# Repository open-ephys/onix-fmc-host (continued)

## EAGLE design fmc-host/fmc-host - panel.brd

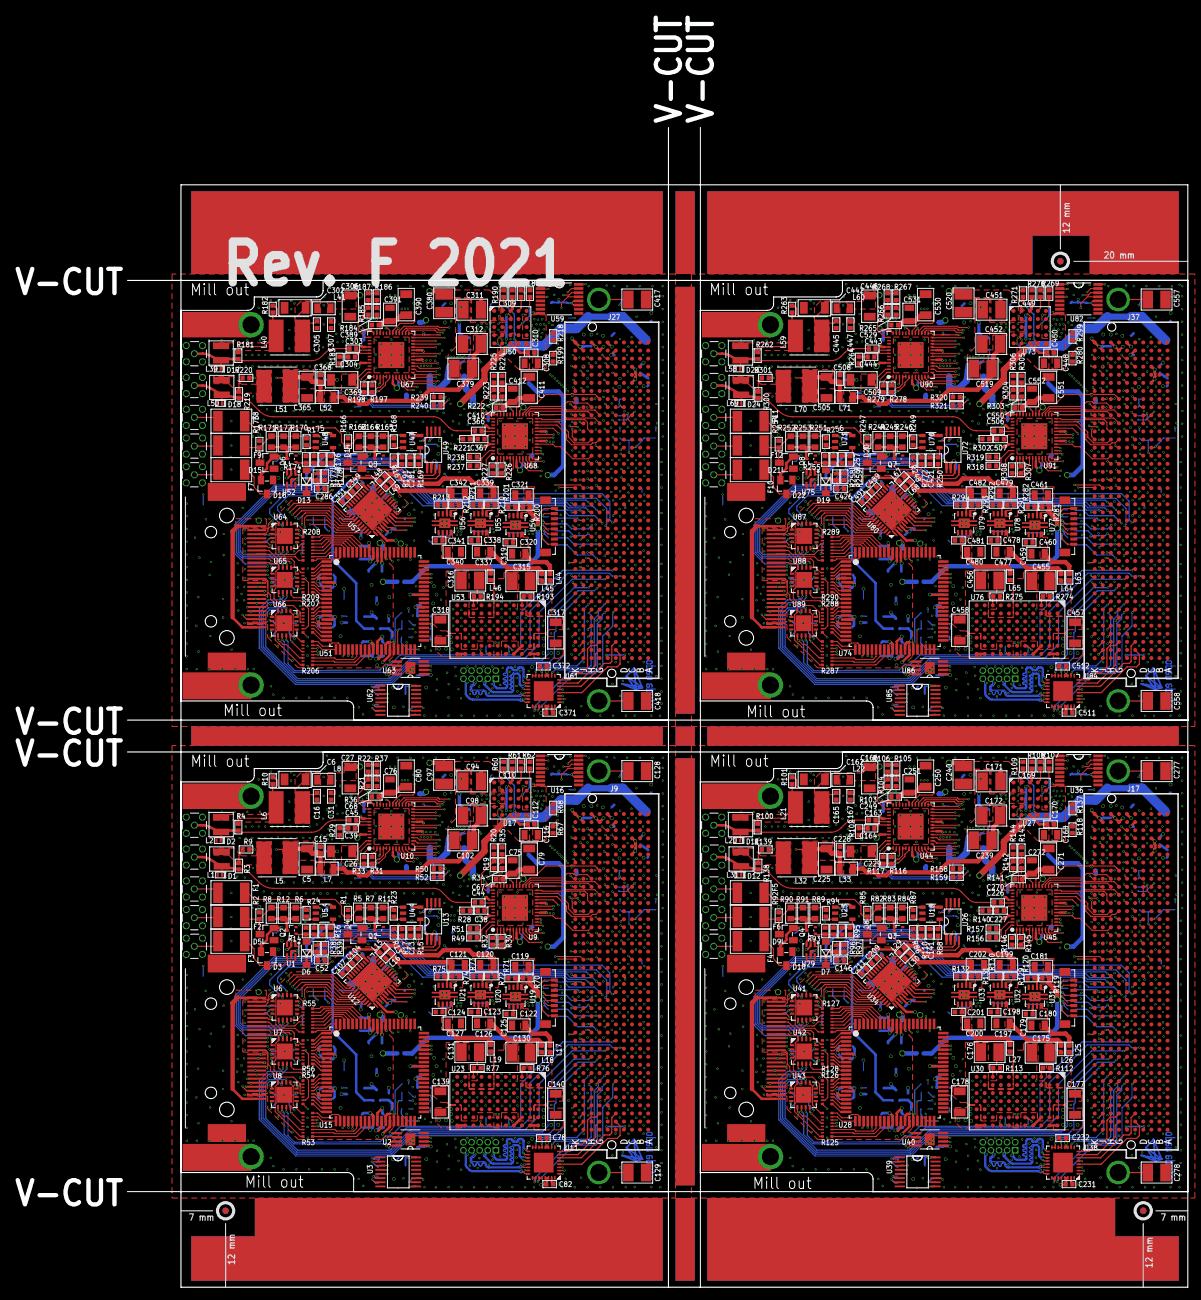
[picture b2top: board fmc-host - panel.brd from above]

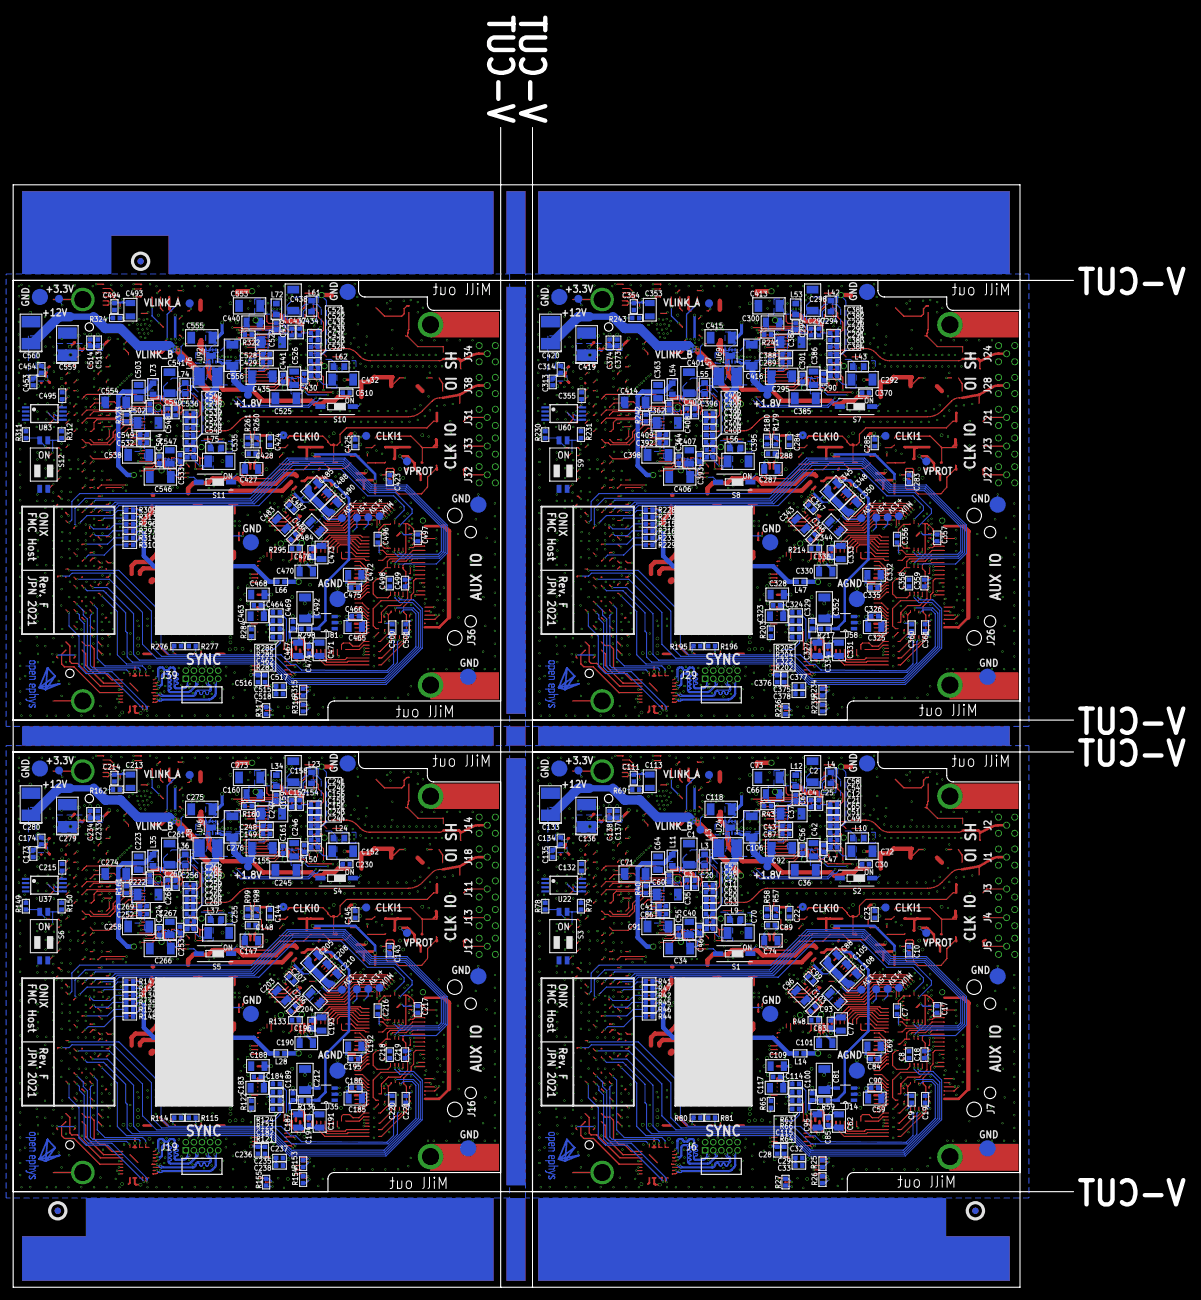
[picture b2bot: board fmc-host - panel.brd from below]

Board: 6 copper layers, 166.4 x 182.0 mm, 1230 parts (611 on the bottom side), 1176 nets.

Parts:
C1, C2, C5, C6, C26, C27, C34, C35, C36, C37, C70, C71, C72, C73, C79, C80, C81, C91, C92, C106, C118, C139, C140, C152, C155, C158, C162, C166, C177, C178, C212, C225, C229, C245, C247, C250, C255, C258, C261, C266, C268, C271, C273, C274, C275, C276, C292, C295, C298, C302, C306, C317, C318, C352, C365, C369, C385, C387, C390, C395, C398, C401, C406, C408, C411, C413, C414, C415, C416, C432, C435, C438, C442, C446, C457, C458, C492, C505, C509, C525, C527, C530, C535, C538, C541, C546, C548, C551, C553, C554, C555, C556: 10uF; 1206
C3, C4, C7, C8, C9, C10, C13, C14, C15, C16, C17, C18, C19, C22, C23, C30, C31, C32, C33, C41, C43, C44, C45, C46, C47, C48, C49, C52, C53, C54, C55, C56, C60, C61, C63, C65, C67, C68, C78, C83, C84, C85, C86, C87, C89, C90, C93, C99, C100, C104, C107, C110, C111, C112, C114, C115, C132, C134, C135, C137, C138, C141, C142, C143, C144, C145, C146, C148, C149, C150, C151, C157, C159, C161, C163, C165, C167, C169, C170, C173, C174, C182, C184, C186, C189, C194, C195, C196, C204, C207, C209, C211, C214, C215, C216, C217, C218, C219, C220, C221, C222, C224, C226, C228, C230, C232, C233, C234, C237, C238, C242, C244, C248, C249, C252, C253, C254, C260, C263, C265, C269, C270, C281, C282, C283, C284, C285, C286, C288, C289, C290, C291, C297, C299, C301, C303, C305, C307, C309, C310, C313, C314, C322, C324, C326, C329, C334, C335, C336, C344, C347, C349, C351, C354, C355, C356, C357, C358, C359, C360, C361, C362, C364, C366, C368, C370, C372, C373, C374, C377, C378, C382, C384, C388, C389, C392, C393, C394, C400, C403, C405, C409, C410, C421, C422, C423, C424, C425, C426, C428, C429, C430, C431, C437, C439, C441, C443, C445, C447, C449, C450, C453, C454, C462, C464, C466, C469, C474, C475, C476, C484, C487, C489, C491, C494, C495, C496, C497, C498, C499, C500, C501, C502, C504, C506, C508, C510, C512, C513, C514, C517, C518, C522, C524, C528, C529, C532, C533, C534, C540, C543, C545, C549, C550: 0.1uF; 0402
C11, C12, C20, C21, C24, C25, C50, C51, C57, C58, C82, C122, C123, C124, C153, C154, C156, C180, C198, C201, C231, C241, C243, C256, C257, C259, C262, C264, C293, C294, C296, C320, C338, C341, C371, C381, C383, C396, C397, C399, C402, C404, C433, C434, C436, C460, C478, C481, C511, C521, C523, C536, C537, C539, C542, C544: 10nF; 0402
C28, C29, C235, C236, C375, C376, C515, C516: 4.7nF; 0402
C38, C39, C164, C227, C304, C367, C444, C507: 47nF; 0402
C40, C42, C64, C66, C74, C75, C76, C88, C147, C160, C205, C223, C246, C251, C267, C272, C287, C300, C345, C363, C386, C391, C407, C412, C427, C440, C485, C503, C526, C531, C547, C552: 1uF; 0805
C59, C62, C69, C77, C95, C96, C101, C103, C105, C108, C109, C113, C116, C117, C119, C120, C121, C125, C126, C127, C168, C179, C181, C183, C185, C187, C188, C190, C191, C192, C193, C197, C199, C200, C202, C203, C206, C208, C210, C213, C308, C319, C321, C323, C325, C327, C328, C330, C331, C332, C333, C337, C339, C340, C342, C343, C346, C348, C350, C353, C448, C459, C461, C463, C465, C467, C468, C470, C471, C472, C473, C477, C479, C480, C482, C483, C486, C488, C490, C493: 10uF; 0805
C94, C97, C98, C102, C130, C131, C171, C172, C175, C176, C239, C240, C311, C312, C315, C316, C379, C380, C451, C452, C455, C456, C519, C520: 47uF; 1210
C128, C129, C277, C278, C417, C418, C557, C558: 0.1uF, 500V; 1210
C133, C136, C279, C280, C419, C420, C559, C560: 33uF; 1411-VISHAY-B
D1, D2, D11, D12, D17, D18, D23, D24: SESD0402X1UN-0020-090; 0402P-DFN
D3, D4, D5, D8, D9, D10, D14, D15, D16, D20, D21, D22: BAR66; SOT23
D6, D7, D13, D19: KDZ4.3B; SOD123
E$1, E$2, E$3, E$4, E$5, E$6: FIDUCIAL
F1, F2, F3, F4, F5, F6, F7, F8, F9, F10, F11, F12: C014F-2; 1812
J1, J2, J3, J4, J5, J11, J12, J13, J14, J18, J21, J22, J23, J24, J28, J31, J32, J33, J34, J38: SMA002; MMCX-THRU
J6, J19, J29, J39: FTSH-105-01-F-D-RA-K
J7, J16, J26, J36: 12226-8250-00FR; 12226-82X0-00XX
J8, J15, J25, J35: FMC_SINGLE_WIDTH_MODULE
J9, J17, J27, J37: ASP-134488-01; FMC_HPC_MALE
J10, J20, J30, J40: BM08B-SURS-TF
L1, L2, L20, L31, L39, L50, L58, L69: 1008PS-472; 1008PS
L3, L4, L9, L10, L11, L12, L23, L24, L34, L35, L36, L37, L42, L43, L53, L54, L55, L56, L61, L62, L72, L73, L74, L75: BLM18KG601SN1D; 0603
L5, L6, L21, L32, L40, L51, L59, L70: SRNxx-101M; SRN6045TA
L7, L8, L22, L33, L41, L52, L60, L71: MPZ2012S102AT000; 0805
L13, L38, L57, L76: 1277AS-H-6R8M=P2; 1210
L14, L15, L16, L17, L18, L19, L25, L26, L27, L28, L29, L30, L44, L45, L46, L47, L48, L49, L63, L64, L65, L66, L67, L68: BLM15PX601SN1D; 0402
Q1, Q2, Q3, Q4, Q5, Q6, Q7, Q8: SI1012R; SC75
R1, R2, R38, R39, R85, R92, R96, R97, R166, R173, R177, R178, R247, R254, R258, R259: 3k; 0402
R3, R4, R9, R10, R57, R58, R98, R99, R100, R101, R138, R139, R179, R180, R181, R182, R219, R220, R260, R261, R262, R263, R300, R301: 2k; 0402
R5, R6, R7, R8, R11, R12, R82, R83, R84, R89, R90, R91, R163, R164, R165, R170, R171, R172, R244, R245, R246, R251, R252, R253: 150,0.25W; 0603
R13, R14, R49, R50, R51, R52, R76, R86, R93, R112, R156, R157, R158, R159, R167, R174, R193, R237, R238, R239, R240, R248, R255, R274, R318, R319, R320, R321: 165k; 0402
R15, R16, R35, R37, R59, R64, R65, R66, R67, R68, R78, R79, R88, R95, R105, R118, R121, R122, R123, R136, R137, R143, R149, R150, R169, R176, R186, R199, R202, R203, R204, R217, R218, R224, R230, R231, R250, R257, R267, R280, R283, R284, R285, R298, R299, R305, R311, R312: 10k; 0402
R17, R18, R41, R42, R44, R45, R46, R47, R110, R111, R134, R135, R147, R148, R151, R152, R191, R192, R215, R216, R228, R229, R232, R233, R272, R273, R296, R297, R309, R310, R313, R314: 1k; 0402
R19, R21, R104, R142, R185, R223, R266, R304: 5.6k 1%; 0402
R20, R22, R106, R144, R187, R225, R268, R306: 21k 1%; 0402
R23, R24, R28, R29, R87, R94, R102, R140, R168, R175, R183, R221, R249, R256, R264, R302: 49.9; 0402
R25, R26, R27, R153, R154, R155, R234, R235, R236, R315, R316, R317: 100; 0402
R30, R31, R32, R33, R40, R43, R71, R73, R75, R116, R117, R120, R130, R132, R145, R146, R160, R161, R197, R198, R201, R211, R213, R226, R227, R241, R242, R278, R279, R282, R292, R294, R307, R308, R322, R323: 4.7k; 0402
R34, R36, R103, R141, R184, R222, R265, R303: DNP; 0402
R48, R63, R124, R133, R205, R214, R286, R295: 0; 0402
R53, R54, R55, R56, R125, R126, R127, R128, R206, R207, R208, R209, R287, R288, R289, R290: 2.2k; RN2X8-1506
R60, R61, R108, R109, R189, R190, R270, R271: 3.48k; 0402
R62, R107, R188, R269: 649k; 0402
R69, R162, R243, R324: 2.2k; 0402
R70, R119, R200, R281: 15k; 0402
R72, R74, R129, R131, R210, R212, R291, R293: 47k; 0402
R77, R113, R194, R275: 178k; 0402
R80, R81, R114, R115, R195, R196, R276, R277: 73.2k; 0402
S1, S2, S4, S5, S7, S8, S10, S11: CHS-01TA; DIP01-SMD-GULL
S3, S6, S9, S12: CHS-02TB
TP1, TP2, TP4, TP5, TP6, TP7, TP11, TP12, TP13, TP14, TP15, TP16, TP19, TP20, TP22, TP23, TP24, TP27, TP28, TP30, TP31, TP32, TP33, TP34, TP37, TP38, TP40, TP41, TP42, TP45, TP46, TP48, TP49, TP50, TP51, TP52, TP55, TP56, TP58, TP59, TP60, TP63, TP64, TP66, TP67, TP68, TP69, TP70: B1,27
TP3, TP8, TP9, TP10, TP17, TP18, TP21, TP25, TP26, TP29, TP35, TP36, TP39, TP43, TP44, TP47, TP53, TP54, TP57, TP61, TP62, TP65, TP71, TP72: B2,54
U1, U29, U52, U75: SN74LVC2G34DCKR; SC70
U2, U40, U63, U86: SN65LVDS9638DGN; MSOP-8-PAD-3X3
U3, U39, U62, U85: FIN1032MTCX; TSSOP-16
U4, U5, U18, U25, U47, U48, U70, U71: ADCMP600; SOT-23-5
U6, U7, U8, U41, U42, U43, U64, U65, U66, U87, U88, U89: DG1412E; QFN16-4X4MM
U9, U10, U44, U45, U67, U68, U90, U91: DS90UB934-Q1; WQFN48-7X7-PAD
U11, U38, U61, U84: DS91M040; WQFN32-5X5
U12, U34, U57, U80: AD5766BCPZ-RL7; CP_40_7
U13, U26, U49, U72: MCP47FEB02A0-E/ST; TSSOP-8
U14, U35, U58, U81: LM4132AMF-2.5/NOPBCT-ND; SOT-23-5
U15, U28, U51, U74: AD7617BSTZ; ST_80_2
U16, U36, U59, U82: AD5142BCPZ10; TSSOP-16_4.4X5.0
U17, U27, U50, U73: LTM4622A; BGA_5X5_625X625
U19, U20, U31, U32, U54, U55, U77, U78: TPS7A49; PVSON-N8+4-3X3
U21, U33, U56, U79: TPS7A30; PVSON-N8+4-3X3
U22, U37, U60, U83: 24AA64ST; TSSOP8
U23, U30, U53, U76: LTM8049_BGA; LTM8049
U24, U46, U69, U92: TPS62061DSGT; WSON8-2X2
X1, X2, X3, X4: OE-LOGO_7X5; OE-LOGO-7X5

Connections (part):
!ADC_CS: J9.H13, U15.63
!ADC_CS1: J17.H13, U28.63
!ADC_CS2: J27.H13, U51.63
!ADC_CS3: J37.H13, U74.63
!ADC_RESET: J9.F10, R66.2
!ADC_RESET1: J17.F10, R123.2
!ADC_RESET2: J27.F10, R204.2
!ADC_RESET3: J37.F10, R285.2
!DAC_CS: J9.J16, U12.8
!DAC_CS1: J17.J16, U34.8
!DAC_CS2: J27.J16, U57.8
!DAC_CS3: J37.J16, U80.8
!DAC_RESET: J9.F14, U12.3
!DAC_RESET1: J17.F14, U34.3
!DAC_RESET2: J27.F14, U57.3
!DAC_RESET3: J37.F14, U80.3
!LINK_PWR_ADJ_CS: J9.F38, U16.16
!LINK_PWR_ADJ_CS1: J17.F38, U36.16
!LINK_PWR_ADJ_CS2: J27.F38, U59.16
!LINK_PWR_ADJ_CS3: J37.F38, U82.16
!LINK_PWR_ADJ_RESET: J9.E37, U16.2
!LINK_PWR_ADJ_RESET1: J17.E37, U36.2
!LINK_PWR_ADJ_RESET2: J27.E37, U59.2
!LINK_PWR_ADJ_RESET3: J37.E37, U82.2
$N1: D5.3, F2.2, R2.2, R6.2, R8.2, R12.2, R24.1
$N2: D3.3, F3.2, U1.4, U1.6
$N3: D4.3, F1.2, R1.2, R5.2, R7.2, R11.2, R23.1
$N4: D8.3, F5.2, R82.2, R83.2, R84.2, R85.2, R87.1
$N5: D9.3, F6.2, R89.2, R90.2, R91.2, R92.2, R94.1
$N6: D10.3, F4.2, U29.4, U29.6
$N7: D14.3, F8.2, R163.2, R164.2, R165.2, R166.2, R168.1
$N8: D15.3, F9.2, R170.2, R171.2, R172.2, R173.2, R175.1
$N9: D16.3, F7.2, U52.4, U52.6
$N10: D20.3, F11.2, R244.2, R245.2, R246.2, R247.2, R249.1
$N11: D21.3, F12.2, R251.2, R252.2, R253.2, R254.2, R256.1
$N12: D22.3, F10.2, U75.4, U75.6
+1V1: C149.2, C155.2, C252.2, C258.2, C276.2, L23.2, L24.1, L36.2, L37.1, L38.1, R103.1, R104.1, R141.1, R142.1, TP34.TP, U44.17, U45.17, U46.4
+1V2: C289.2, C295.2, C392.2, C398.2, C416.2, L42.2, L43.1, L55.2, L56.1, L57.1, R184.1, R185.1, R222.1, R223.1, TP52.TP, U67.17, U68.17, U69.4
+1V3: C429.2, C435.2, C532.2, C538.2, C556.2, L61.2, L62.1, L74.2, L75.1, L76.1, R265.1, R266.1, R303.1, R304.1, TP70.TP, U90.17, U91.17, U92.4
+1V8: C86.2, C87.2, C91.2, C92.2, C106.2, L3.2, L4.2, L9.1, L10.1, L13.1, R19.1, R21.1, R34.1, R36.1, TP16.TP, U9.17, U10.17, U24.4
+3V1: C143.2, C144.1, C145.1, C147.2, C148.2, C177.1, C178.1, C183.2, C184.2, C203.2, C204.2, C213.2, C214.2, C231.2, C232.2, C233.2, C234.2, C235.1, C236.1, C237.1, C238.1, C275.2, C279.A, J17.E39, J17.F40, J17.G39, J17.H40, J17.J39, J17.K40, L34.1, L35.1, R98.2, R99.2, R116.2, R117.2, R121.1, R122.1, R124.1, R145.2, R146.2, R149.2, R150.2, R160.2, R161.2, R162.1, S4.2, S5.2, TP27.TP, U18.5, U25.5, U26.1, U26.2, U28.49, U29.5, U30.A5, U30.A6, U30.A7, U30.B7, U30.K7, U30.L5, U30.L6, U30.L7, U34.4, U36.1, U36.11, U36.12, U38.11, U38.12, U38.29, U38.30, U39.4, U39.16, U40.1, U44.4, U44.5, U45.4, U45.5, U46.5, U46.6, U46.7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
+3V2: C283.2, C284.1, C285.1, C287.2, C288.2, C317.1, C318.1, C323.2, C324.2, C343.2, C344.2, C353.2, C354.2, C371.2, C372.2, C373.2, C374.2, C375.1, C376.1, C377.1, C378.1, C415.2, C419.A, J27.E39, J27.F40, J27.G39, J27.H40, J27.J39, J27.K40, L53.1, L54.1, R179.2, R180.2, R197.2, R198.2, R202.1, R203.1, R205.1, R226.2, R227.2, R230.2, R231.2, R241.2, R242.2, R243.1, S7.2, S8.2, TP45.TP, U47.5, U48.5, U49.1, U49.2, U51.49, U52.5, U53.A5, U53.A6, U53.A7, U53.B7, U53.K7, U53.L5, U53.L6, U53.L7, U57.4, U59.1, U59.11, U59.12, U61.11, U61.12, U61.29, U61.30, U62.4, U62.16, U63.1, U67.4, U67.5, U68.4, U68.5, U69.5, U69.6, U69.7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
+3V3: C10.2, C22.1, C23.1, C28.1, C29.1, C32.1, C33.1, C74.2, C78.2, C82.2, C89.2, C93.2, C96.2, C111.2, C113.2, C114.2, C117.2, C118.2, C136.A, C137.2, C138.2, C139.1, C140.1, J9.E39, J9.F40, J9.G39, J9.H40, J9.J39, J9.K40, L11.1, L12.1, R30.2, R31.2, R32.2, R33.2, R40.2, R43.2, R57.2, R58.2, R63.1, R64.1, R65.1, R69.1, R78.2, R79.2, S1.2, S2.2, TP11.TP, U1.5, U2.1, U3.4, U3.16, U4.5, U5.5, U9.4, U9.5, U10.4, U10.5, U11.11, U11.12, U11.29, U11.30, U12.4, U13.1, U13.2, U15.49, U16.1, U16.11, U16.12, U23.A5, U23.A6, U23.A7, U23.B7, U23.K7, U23.L5, U23.L6, U23.L7, U24.5, U24.6, U24.7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
+3V4: C423.2, C424.1, C425.1, C427.2, C428.2, C457.1, C458.1, C463.2, C464.2, C483.2, C484.2, C493.2, C494.2, C511.2, C512.2, C513.2, C514.2, C515.1, C516.1, C517.1, C518.1, C555.2, C559.A, J37.E39, J37.F40, J37.G39, J37.H40, J37.J39, J37.K40, L72.1, L73.1, R260.2, R261.2, R278.2, R279.2, R283.1, R284.1, R286.1, R307.2, R308.2, R311.2, R312.2, R322.2, R323.2, R324.1, S10.2, S11.2, TP63.TP, U70.5, U71.5, U72.1, U72.2, U74.49, U75.5, U76.A5, U76.A6, U76.A7, U76.B7, U76.K7, U76.L5, U76.L6, U76.L7, U80.4, U82.1, U82.11, U82.12, U84.11, U84.12, U84.29, U84.30, U85.4, U85.16, U86.1, U90.4, U90.5, U91.4, U91.5, U92.5, U92.6, U92.7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
+5V_AN: C59.2, C62.2, C69.2, C77.2, C81.1, C83.2, C84.2, C85.2, C90.2, C107.2, C108.2, L14.1, TP1.TP, U12.28, U14.3, U14.4, U15.6, U15.15, U15.30, U15.71
+5V_AN1: C185.2, C186.2, C191.2, C192.2, C193.2, C194.2, C195.2, C196.2, C210.2, C211.2, C212.1, L28.1, TP19.TP, U28.6, U28.15, U28.30, U28.71, U34.28, U35.3, U35.4
+5V_AN2: C325.2, C326.2, C331.2, C332.2, C333.2, C334.2, C335.2, C336.2, C350.2, C351.2, C352.1, L47.1, TP37.TP, U51.6, U51.15, U51.30, U51.71, U57.28, U58.3, U58.4
+5V_AN3: C465.2, C466.2, C471.2, C472.2, C473.2, C474.2, C475.2, C476.2, C490.2, C491.2, C492.1, L66.1, TP55.TP, U74.6, U74.15, U74.30, U74.71, U80.28, U81.3, U81.4
+12V: C116.2, C133.A, C134.2, C135.2, J7.1, J7.26, J9.C35, J9.C37, R38.2, R39.2, TP12.TP, U17.A2, U17.B3, U17.D3, U17.E2
+12V1: C168.2, C173.2, C174.2, C280.A, J16.1, J16.26, J17.C35, J17.C37, R96.2, R97.2, TP28.TP, U27.A2, U27.B3, U27.D3, U27.E2
+12V2: C308.2, C313.2, C314.2, C420.A, J26.1, J26.26, J27.C35, J27.C37, R177.2, R178.2, TP46.TP, U50.A2, U50.B3, U50.D3, U50.E2
+12V3: C448.2, C453.2, C454.2, C560.A, J36.1, J36.26, J37.C35, J37.C37, R258.2, R259.2, TP64.TP, U73.A2, U73.B3, U73.D3, U73.E2
+13V_AN: C7.2, C8.2, C9.2, C104.2, C105.2, L15.1, TP2.TP, U6.11, U7.11, U8.11, U12.26
+13V_AN1: C208.2, C209.2, C216.2, C218.2, C220.2, L29.1, TP20.TP, U34.26, U41.11, U42.11, U43.11
+13V_AN2: C348.2, C349.2, C356.2, C358.2, C360.2, L48.1, TP38.TP, U57.26, U64.11, U65.11, U66.11
+13V_AN3: C488.2, C489.2, C496.2, C498.2, C500.2, L67.1, TP56.TP, U80.26, U87.11, U88.11, U89.11
+15V: C130.2, L17.2, L18.2, R76.1, U23.A1, U23.A2, U23.B1, U23.B2
+15V1: C175.2, L25.2, L26.2, R112.1, U30.A1, U30.A2, U30.B1, U30.B2
+15V2: C315.2, L44.2, L45.2, R193.1, U53.A1, U53.A2, U53.B1, U53.B2
+15V3: C455.2, L63.2, L64.2, R274.1, U76.A1, U76.A2, U76.B1, U76.B2
-13V_AN: C17.2, C18.2, C19.2, C99.2, C103.2, L16.1, TP4.TP, U6.2, U6.PAD, U7.2, U7.PAD, U8.2, U8.PAD, U12.6, U12.PAD
-13V_AN1: C206.2, C207.2, C217.2, C219.2, C221.2, L30.1, TP22.TP, U34.6, U34.PAD, U41.2, U41.PAD, U42.2, U42.PAD, U43.2, U43.PAD
-13V_AN2: C346.2, C347.2, C357.2, C359.2, C361.2, L49.1, TP40.TP, U57.6, U57.PAD, U64.2, U64.PAD, U65.2, U65.PAD, U66.2, U66.PAD
-13V_AN3: C486.2, C487.2, C497.2, C499.2, C501.2, L68.1, TP58.TP, U80.6, U80.PAD, U87.2, U87.PAD, U88.2, U88.PAD, U89.2, U89.PAD
-15V: C131.1, L19.2, R77.1, U23.G1, U23.G2, U23.H1, U23.H2, U23.J2
-15V1: C176.1, L27.2, R113.1, U30.G1, U30.G2, U30.H1, U30.H2, U30.J2
-15V2: C316.1, L46.2, R194.1, U53.G1, U53.G2, U53.H1, U53.H2, U53.J2
-15V3: C456.1, L65.2, R275.1, U76.G1, U76.G2, U76.H1, U76.H2, U76.J2
ADC_BUSY: J9.J12, U15.67
ADC_BUSY1: J17.J12, U28.67
ADC_BUSY2: J27.J12, U51.67
ADC_BUSY3: J37.J12, U74.67
ADC_CONVST: J9.K13, U15.68
ADC_CONVST1: J17.K13, U28.68
ADC_CONVST2: J27.K13, U51.68
ADC_CONVST3: J37.K13, U74.68
ADC_MISO_A: J9.K11, U15.57
ADC_MISO_A1: J17.K11, U28.57
ADC_MISO_A2: J27.K11, U51.57
ADC_MISO_A3: J37.K11, U74.57
ADC_MISO_B: J9.J10, U15.56
ADC_MISO_B1: J17.J10, U28.56
ADC_MISO_B2: J27.J10, U51.56
ADC_MISO_B3: J37.J10, U74.56
ADC_MOSI: J9.K10, U15.55
ADC_MOSI1: J17.K10, U28.55
ADC_MOSI2: J27.K10, U51.55
ADC_MOSI3: J37.K10, U74.55
ADC_SCLK: J9.J13, U15.62
ADC_SCLK1: J17.J13, U28.62
ADC_SCLK2: J27.J13, U51.62
ADC_SCLK3: J37.J13, U74.62
ADDR0: J9.C27, R78.1, S3.4
ADDR1: J9.C26, R79.1, S3.3
ADDR2: J17.C27, R149.1, S6.4
ADDR3: J17.C26, R150.1, S6.3
ADDR4: J27.C27, R230.1, S9.4
ADDR5: J27.C26, R231.1, S9.3
ADDR6: J37.C27, R311.1, S12.4
ADDR7: J37.C26, R312.1, S12.3
AGND: C7.1, C8.1, C9.1, C17.1, C18.1, C19.1, C59.1, C62.1, C69.1, C77.1, C81.2, C83.1, C84.1, C85.1, C88.1, C90.1, C95.1, C99.1, C100.1, C101.1, C103.1, C104.1, C105.1, C107.1, C108.1, J7.13, J7.14, R48.1, R53.C2, R53.C4, R53.C6, R53.C7, R54.C1, R54.C3, R54.C5, R54.C6, R54.C7, R54.C8, R55.C2, R55.C3, R55.C5, R55.C7, R56.C1, R56.C2, R56.C3, R56.C4, R56.C6, R56.C8, TP3.TP, U6.3, U7.3, U8.3, U12.10, U12.20, U12.23, U12.24, U12.25, U12.29, U12.31, U14.2, U15.5, U15.16, U15.29, U15.32, U15.34, U15.69, U15.72
AGND1: C185.1, C186.1, C187.1, C189.1, C190.1, C191.1, C192.1, C193.1, C194.1, C195.1, C196.1, C205.1, C206.1, C207.1, C208.1, C209.1, C210.1, C211.1, C212.2, C216.1, C217.1, C218.1, C219.1, C220.1, C221.1, J16.13, J16.14, R125.C2, R125.C4, R125.C6, R125.C7, R126.C1, R126.C3, R126.C5, R126.C6, R126.C7, R126.C8, R127.C2, R127.C3, R127.C5, R127.C7, R128.C1, R128.C2, R128.C3, R128.C4, R128.C6, R128.C8, R133.1, TP21.TP, U28.5, U28.16, U28.29, U28.32, U28.34, U28.69, U28.72, U34.10, U34.20, U34.23, U34.24, U34.25, U34.29, U34.31, U35.2, U41.3, U42.3, U43.3
AGND2: C325.1, C326.1, C327.1, C329.1, C330.1, C331.1, C332.1, C333.1, C334.1, C335.1, C336.1, C345.1, C346.1, C347.1, C348.1, C349.1, C350.1, C351.1, C352.2, C356.1, C357.1, C358.1, C359.1, C360.1, C361.1, J26.13, J26.14, R206.C2, R206.C4, R206.C6, R206.C7, R207.C1, R207.C3, R207.C5, R207.C6, R207.C7, R207.C8, R208.C2, R208.C3, R208.C5, R208.C7, R209.C1, R209.C2, R209.C3, R209.C4, R209.C6, R209.C8, R214.1, TP39.TP, U51.5, U51.16, U51.29, U51.32, U51.34, U51.69, U51.72, U57.10, U57.20, U57.23, U57.24, U57.25, U57.29, U57.31, U58.2, U64.3, U65.3, U66.3
AGND3: C465.1, C466.1, C467.1, C469.1, C470.1, C471.1, C472.1, C473.1, C474.1, C475.1, C476.1, C485.1, C486.1, C487.1, C488.1, C489.1, C490.1, C491.1, C492.2, C496.1, C497.1, C498.1, C499.1, C500.1, C501.1, J36.13, J36.14, R287.C2, R287.C4, R287.C6, R287.C7, R288.C1, R288.C3, R288.C5, R288.C6, R288.C7, R288.C8, R289.C2, R289.C3, R289.C5, R289.C7, R290.C1, R290.C2, R290.C3, R290.C4, R290.C6, R290.C8, R295.1, TP57.TP, U74.5, U74.16, U74.29, U74.32, U74.34, U74.69, U74.72, U80.10, U80.20, U80.23, U80.24, U80.25, U80.29, U80.31, U81.2, U87.3, U88.3, U89.3
AIN_AOUT0: J9.F11, U8.15
AIN_AOUT1: J9.D11, U8.6
AIN_AOUT2: J9.E12, U8.7
AIN_AOUT3: J9.H10, U8.14
AIN_AOUT4: J9.E18, U7.15
AIN_AOUT5: J9.J9, U7.6
AIN_AOUT6: J9.G10, U7.7
AIN_AOUT7: J9.F17, U7.14
AIN_AOUT8: J9.H20, U6.7
AIN_AOUT9: J9.J19, U6.14
AIN_AOUT10: J9.G19, U6.6
AIN_AOUT11: J9.H19, U6.15
AIN_AOUT12: J17.H19, U41.15
AIN_AOUT13: J17.G19, U41.6
AIN_AOUT14: J17.J19, U41.14
AIN_AOUT15: J17.H20, U41.7
AIN_AOUT16: J17.E18, U42.15
AIN_AOUT17: J17.F17, U42.14
AIN_AOUT18: J17.G10, U42.7
AIN_AOUT19: J17.F11, U43.15
AIN_AOUT20: J17.H10, U43.14
AIN_AOUT21: J17.E12, U43.7
AIN_AOUT22: J17.J9, U42.6
AIN_AOUT23: J17.D11, U43.6
AIN_AOUT24: J27.H19, U64.15
AIN_AOUT25: J27.G19, U64.6
AIN_AOUT26: J27.J19, U64.14
AIN_AOUT27: J27.H20, U64.7
AIN_AOUT28: J27.E18, U65.15
AIN_AOUT29: J27.F17, U65.14
AIN_AOUT30: J27.G10, U65.7
AIN_AOUT31: J27.F11, U66.15
AIN_AOUT32: J27.H10, U66.14
AIN_AOUT33: J27.E12, U66.7
AIN_AOUT34: J27.J9, U65.6
AIN_AOUT35: J27.D11, U66.6
AIN_AOUT36: J37.H19, U87.15
AIN_AOUT37: J37.G19, U87.6
AIN_AOUT38: J37.J19, U87.14
AIN_AOUT39: J37.H20, U87.7
AIN_AOUT40: J37.E18, U88.15
AIN_AOUT41: J37.F17, U88.14
AIN_AOUT42: J37.G10, U88.7
AIN_AOUT43: J37.F11, U89.15
AIN_AOUT44: J37.H10, U89.14
AIN_AOUT45: J37.E12, U89.7
AIN_AOUT46: J37.J9, U88.6
AIN_AOUT47: J37.D11, U89.6
AIO_0: J7.7, R53.C1, U8.16
AIO_1: J7.20, R53.C3, U8.5
AIO_2: J7.8, R53.C5, U8.8
AIO_3: J7.21, R53.C8, U8.13
AIO_4: J7.9, R54.C4, U7.16
AIO_5: J7.22, R54.C2, U7.5
AIO_6: J7.10, R56.C5, U7.8
AIO_7: J7.23, R56.C7, U7.13
AIO_8: J7.11, R55.C6, U6.8
AIO_9: J7.24, R55.C8, U6.13
AIO_10: J7.12, R55.C4, U6.5
AIO_11: J7.25, R55.C1, U6.16
AIO_12: J16.25, R127.C1, U41.16
AIO_13: J16.12, R127.C4, U41.5
AIO_14: J16.24, R127.C8, U41.13
AIO_15: J16.11, R127.C6, U41.8
AIO_16: J16.23, R128.C7, U42.13
AIO_17: J16.10, R128.C5, U42.8
AIO_18: J16.22, R126.C2, U42.5
AIO_19: J16.9, R126.C4, U42.16
AIO_20: J16.21, R125.C8, U43.13
AIO_21: J16.8, R125.C5, U43.8
AIO_22: J16.20, R125.C3, U43.5
AIO_23: J16.7, R125.C1, U43.16
AIO_24: J26.25, R208.C1, U64.16
AIO_25: J26.12, R208.C4, U64.5
AIO_26: J26.24, R208.C8, U64.13
AIO_27: J26.11, R208.C6, U64.8
AIO_28: J26.23, R209.C7, U65.13
AIO_29: J26.10, R209.C5, U65.8
AIO_30: J26.22, R207.C2, U65.5
AIO_31: J26.9, R207.C4, U65.16
AIO_32: J26.21, R206.C8, U66.13
AIO_33: J26.8, R206.C5, U66.8
AIO_34: J26.20, R206.C3, U66.5
AIO_35: J26.7, R206.C1, U66.16
AIO_36: J36.25, R289.C1, U87.16
AIO_37: J36.12, R289.C4, U87.5
AIO_38: J36.24, R289.C8, U87.13
AIO_39: J36.11, R289.C6, U87.8
AIO_40: J36.23, R290.C7, U88.13
AIO_41: J36.10, R290.C5, U88.8
AIO_42: J36.22, R288.C2, U88.5
AIO_43: J36.9, R288.C4, U88.16
AIO_44: J36.21, R287.C8, U89.13
AIO_45: J36.8, R287.C5, U89.8
AIO_46: J36.20, R287.C3, U89.5
AIO_47: J36.7, R287.C1, U89.16
AOUT0: U6.1, U12.32
AOUT1: U6.4, U12.33
AOUT2: U6.9, U12.34
AOUT3: U6.12, U12.35
AOUT4: U7.1, U12.36
AOUT5: U7.4, U12.37
AOUT6: U7.12, U12.38
AOUT7: U7.9, U12.39
AOUT8: U8.9, U12.12
AOUT9: U8.12, U12.13
AOUT10: U8.4, U12.14
AOUT11: U8.1, U12.15
AOUT12: U34.33, U41.4
AOUT13: U34.34, U41.9
AOUT14: U34.36, U42.1
AOUT15: U34.38, U42.12
AOUT16: U34.37, U42.4
AOUT17: U34.35, U41.12
AOUT18: U34.32, U41.1
AOUT19: U34.39, U42.9
AOUT20: U34.12, U43.9
AOUT21: U34.13, U43.12
AOUT22: U34.14, U43.4
AOUT23: U34.15, U43.1
AOUT24: U57.33, U64.4
AOUT25: U57.34, U64.9
AOUT26: U57.36, U65.1
AOUT27: U57.38, U65.12
AOUT28: U57.37, U65.4
AOUT29: U57.35, U64.12
AOUT30: U57.32, U64.1
AOUT31: U57.39, U65.9
AOUT32: U57.12, U66.9
AOUT33: U57.13, U66.12
AOUT34: U57.14, U66.4
AOUT35: U57.15, U66.1
AOUT36: U80.33, U87.4
AOUT37: U80.34, U87.9
AOUT38: U80.36, U88.1
AOUT39: U80.38, U88.12
AOUT40: U80.37, U88.4
AOUT41: U80.35, U87.12
AOUT42: U80.32, U87.1
AOUT43: U80.39, U88.9
AOUT44: U80.12, U89.9
AOUT45: U80.13, U89.12
AOUT46: U80.14, U89.4
AOUT47: U80.15, U89.1
CLKIN0: J9.D21, TP7.TP, U4.1
CLKIN1: J9.E19, TP6.TP, U5.1
CLKIN2: J17.D21, TP31.TP, U18.1
CLKIN3: J17.E19, TP30.TP, U25.1
CLKIN4: J27.D21, TP49.TP, U47.1
CLKIN5: J27.E19, TP48.TP, U48.1
CLKIN6: J37.D21, TP67.TP, U70.1
CLKIN7: J37.E19, TP66.TP, U71.1
CLKIN_TERM0: J9.K19, R17.1
CLKIN_TERM1: J9.K17, R18.1
CLKIN_TERM2: J17.K19, R110.1
CLKIN_TERM3: J17.K17, R111.1
CLKIN_TERM4: J27.K19, R191.1
CLKIN_TERM5: J27.K17, R192.1
CLKIN_TERM6: J37.K19, R272.1
CLKIN_TERM7: J37.K17, R273.1
CLKIN_VBIAS_SCL: J9.J21, R58.1, U13.7
CLKIN_VBIAS_SCL1: J17.J21, R99.1, U26.7
CLKIN_VBIAS_SCL2: J27.J21, R180.1, U49.7
CLKIN_VBIAS_SCL3: J37.J21, R261.1, U72.7
CLKIN_VBIAS_SDA: J9.K20, R57.1, U13.8
CLKIN_VBIAS_SDA1: J17.K20, R98.1, U26.8
CLKIN_VBIAS_SDA2: J27.K20, R179.1, U49.8
CLKIN_VBIAS_SDA3: J37.K20, R260.1, U72.8
CLKOUT: J9.D20, U1.1, U1.3
CLKOUT1: J17.D20, U29.1, U29.3
CLKOUT2: J27.D20, U52.1, U52.3
CLKOUT3: J37.D20, U75.1, U75.3
DAC_MISO: J9.K16, U12.9
DAC_MISO1: J17.K16, U34.9
DAC_MISO2: J27.K16, U57.9
DAC_MISO3: J37.K16, U80.9
DAC_MOSI: J9.H14, U12.5
DAC_MOSI1: J17.H14, U34.5
DAC_MOSI2: J27.H14, U57.5
DAC_MOSI3: J37.H14, U80.5
DAC_MUX: TP15.TP, U12.27
DAC_MUX1: TP33.TP, U34.27
DAC_MUX2: TP51.TP, U57.27
DAC_MUX3: TP69.TP, U80.27
DAC_SCLK: J9.J15, U12.7
DAC_SCLK1: J17.J15, U34.7
DAC_SCLK2: J27.J15, U57.7
DAC_SCLK3: J37.J15, U80.7
DES_A_D0: J9.F34, U10.24
DES_A_D1: J9.K35, U10.23
DES_A_D2: J9.J34, U10.22
DES_A_D3: J9.K34, U10.21
DES_A_D4: J9.E33, U10.19
DES_A_D5: J9.J33, U10.18
DES_A_D6: J9.F32, U10.16
DES_A_D7: J9.E31, U10.15
DES_A_D8: J9.K32, U10.14
DES_A_D9: J9.F31, U10.13
DES_A_D10: J9.J31, U10.12
DES_A_D11: J9.K31, U10.11
DES_A_D12: J17.K35, U44.23
DES_A_D13: J17.J31, U44.12
DES_A_D14: J17.F34, U44.24
DES_A_D15: J17.J34, U44.22
DES_A_D16: J17.K34, U44.21
DES_A_D17: J17.E33, U44.19
DES_A_D18: J17.J33, U44.18
DES_A_D19: J17.F32, U44.16
DES_A_D20: J17.E31, U44.15
DES_A_D21: J17.K32, U44.14
DES_A_D22: J17.F31, U44.13
DES_A_D23: J17.K31, U44.11
DES_A_D24: J27.K35, U67.23
DES_A_D25: J27.J31, U67.12
DES_A_D26: J27.F34, U67.24
DES_A_D27: J27.J34, U67.22
DES_A_D28: J27.K34, U67.21
DES_A_D29: J27.E33, U67.19
DES_A_D30: J27.J33, U67.18
DES_A_D31: J27.F32, U67.16
DES_A_D32: J27.E31, U67.15
DES_A_D33: J27.K32, U67.14
DES_A_D34: J27.F31, U67.13
DES_A_D35: J27.K31, U67.11
DES_A_D36: J37.K35, U90.23
DES_A_D37: J37.J31, U90.12
DES_A_D38: J37.F34, U90.24
DES_A_D39: J37.J34, U90.22
DES_A_D40: J37.K34, U90.21
DES_A_D41: J37.E33, U90.19
DES_A_D42: J37.J33, U90.18
DES_A_D43: J37.F32, U90.16
DES_A_D44: J37.E31, U90.15
DES_A_D45: J37.K32, U90.14
DES_A_D46: J37.F31, U90.13
DES_A_D47: J37.K31, U90.11
DES_A_GPIO0: J9.J37, U10.28
DES_A_GPIO1: J9.K37, U10.27
DES_A_GPIO2: J9.J36, U10.26
DES_A_GPIO3: J9.E34, R43.1, U10.25
DES_A_GPIO4: J17.J37, U44.28
DES_A_GPIO5: J17.K37, U44.27
DES_A_GPIO6: J17.J36, U44.26
DES_A_GPIO7: J17.E34, R160.1, U44.25
DES_A_GPIO8: J27.J37, U67.28
DES_A_GPIO9: J27.K37, U67.27
DES_A_GPIO10: J27.J36, U67.26
DES_A_GPIO11: J27.E34, R241.1, U67.25
DES_A_GPIO12: J37.J37, U90.28
DES_A_GPIO13: J37.K37, U90.27
DES_A_GPIO14: J37.J36, U90.26
DES_A_GPIO15: J37.E34, R322.1, U90.25
DES_A_HSYNC: J9.E30, U10.10
DES_A_HSYNC1: J17.E30, U44.10
DES_A_HSYNC2: J27.E30, U67.10
DES_A_HSYNC3: J37.E30, U90.10
DES_A_LOCK: J9.E27, R50.2, U10.48
DES_A_LOCK1: J17.E27, R158.2, U44.48
DES_A_LOCK2: J27.E27, R239.2, U67.48
DES_A_LOCK3: J37.E27, R320.2, U90.48
DES_A_PASS: J9.J28, R52.2, U10.47
DES_A_PASS1: J17.J28, R159.2, U44.47
DES_A_PASS2: J27.J28, R240.2, U67.47
DES_A_PASS3: J37.J28, R321.2, U90.47
DES_A_PCLK: J9.K28, U10.8
DES_A_PCLK1: J17.K28, U44.8
DES_A_PCLK2: J27.K28, U67.8
DES_A_PCLK3: J37.K28, U90.8
DES_A_PDB: J9.F35, U10.30
DES_A_PDB1: J17.F35, U44.30
DES_A_PDB2: J27.F35, U67.30
DES_A_PDB3: J37.F35, U90.30
DES_A_SCL: J9.F29, R31.1, U10.2
DES_A_SCL1: J17.F29, R116.1, U44.2
DES_A_SCL2: J27.F29, R197.1, U67.2
DES_A_SCL3: J37.F29, R278.1, U90.2
DES_A_SDA\: J9.E28, R33.1, U10.1
DES_A_SDA\1: J17.E28, R117.1, U44.1
DES_A_SDA\2: J27.E28, R198.1, U67.1
DES_A_SDA\3: J37.E28, R279.1, U90.1
DES_A_VSYNC: J9.J30, U10.9
DES_A_VSYNC1: J17.J30, U44.9
DES_A_VSYNC2: J27.J30, U67.9
DES_A_VSYNC3: J37.J30, U90.9
DES_B_D0: J9.H29, U9.24
DES_B_D1: J9.H28, U9.23
DES_B_D2: J9.G28, U9.22
DES_B_D3: J9.G27, U9.21
DES_B_D4: J9.D27, U9.19
DES_B_D5: J9.D26, U9.18
DES_B_D6: J9.H26, U9.16
DES_B_D7: J9.G25, U9.15
DES_B_D8: J9.H25, U9.14
DES_B_D9: J9.D24, U9.13
DES_B_D10: J9.G24, U9.12
DES_B_D11: J9.D23, U9.11
DES_B_D12: J17.H28, U45.23
DES_B_D13: J17.H29, U45.24
DES_B_D14: J17.G28, U45.22
DES_B_D15: J17.G27, U45.21
DES_B_D16: J17.D27, U45.19
DES_B_D17: J17.H26, U45.16
DES_B_D18: J17.D26, U45.18
DES_B_D19: J17.G25, U45.15
DES_B_D20: J17.H25, U45.14
DES_B_D21: J17.D24, U45.13
DES_B_D22: J17.G24, U45.12
DES_B_D23: J17.D23, U45.11
DES_B_D24: J27.H28, U68.23
DES_B_D25: J27.H29, U68.24
DES_B_D26: J27.G28, U68.22
DES_B_D27: J27.G27, U68.21
DES_B_D28: J27.D27, U68.19
DES_B_D29: J27.H26, U68.16
DES_B_D30: J27.D26, U68.18
DES_B_D31: J27.G25, U68.15
DES_B_D32: J27.H25, U68.14
DES_B_D33: J27.D24, U68.13
DES_B_D34: J27.G24, U68.12
DES_B_D35: J27.D23, U68.11
DES_B_D36: J37.H28, U91.23
DES_B_D37: J37.H29, U91.24
DES_B_D38: J37.G28, U91.22
DES_B_D39: J37.G27, U91.21
DES_B_D40: J37.D27, U91.19
DES_B_D41: J37.H26, U91.16
DES_B_D42: J37.D26, U91.18
DES_B_D43: J37.G25, U91.15
DES_B_D44: J37.H25, U91.14
DES_B_D45: J37.D24, U91.13
DES_B_D46: J37.G24, U91.12
DES_B_D47: J37.D23, U91.11
DES_B_GPIO0: J9.H32, U9.28
DES_B_GPIO1: J9.G31, U9.27
DES_B_GPIO2: J9.H31, U9.26
DES_B_GPIO3: J9.G30, R40.1, U9.25
DES_B_GPIO4: J17.G30, R161.1, U45.25
DES_B_GPIO5: J17.H31, U45.26
DES_B_GPIO6: J17.G31, U45.27
DES_B_GPIO7: J17.H32, U45.28
DES_B_GPIO8: J27.G30, R242.1, U68.25
DES_B_GPIO9: J27.H31, U68.26
DES_B_GPIO10: J27.G31, U68.27
DES_B_GPIO11: J27.H32, U68.28
DES_B_GPIO12: J37.G30, R323.1, U91.25
DES_B_GPIO13: J37.H31, U91.26
DES_B_GPIO14: J37.G31, U91.27
DES_B_GPIO15: J37.H32, U91.28
DES_B_HSYNC\: J9.H23, U9.10
DES_B_HSYNC\1: J17.H23, U45.10
DES_B_HSYNC\2: J27.H23, U68.10
DES_B_HSYNC\3: J37.H23, U91.10
DES_B_LOCK: J9.J22, R49.2, U9.48
DES_B_LOCK1: J17.J22, R156.2, U45.48
DES_B_LOCK2: J27.J22, R237.2, U68.48
DES_B_LOCK3: J37.J22, R318.2, U91.48
DES_B_PASS: J9.K22, R51.2, U9.47
DES_B_PASS1: J17.K22, R157.2, U45.47
DES_B_PASS2: J27.K22, R238.2, U68.47
DES_B_PASS3: J37.K22, R319.2, U91.47
DES_B_PCLK: J9.C22, U9.8
DES_B_PCLK1: J17.C22, U45.8
DES_B_PCLK2: J27.C22, U68.8
DES_B_PCLK3: J37.C22, U91.8
DES_B_PDB: J9.G33, U9.30
DES_B_PDB1: J17.G33, U45.30
DES_B_PDB2: J27.G33, U68.30
DES_B_PDB3: J37.G33, U91.30
DES_B_SCL: J9.G22, R30.1, U9.2
DES_B_SCL1: J17.G22, R145.1, U45.2
DES_B_SCL2: J27.G22, R226.1, U68.2
DES_B_SCL3: J37.G22, R307.1, U91.2
DES_B_SDA: J9.H22, R32.1, U9.1
DES_B_SDA1: J17.H22, R146.1, U45.1
DES_B_SDA2: J27.H22, R227.1, U68.1
DES_B_SDA3: J37.H22, R308.1, U91.1
DES_B_VSYNC: J9.K23, U9.9
DES_B_VSYNC1: J17.K23, U45.9
DES_B_VSYNC2: J27.K23, U68.9
DES_B_VSYNC3: J37.K23, U91.9
DI_VBIAS0: R15.1, U13.3
DI_VBIAS1: R16.1, U13.4
DI_VBIAS2: R88.1, U26.3
DI_VBIAS3: R95.1, U26.4
DI_VBIAS4: R169.1, U49.3
DI_VBIAS5: R176.1, U49.4
DI_VBIAS6: R250.1, U72.3
DI_VBIAS7: R257.1, U72.4
DOUTP_F_A: C45.2, D2.C, J2.SIG, L2.2, R4.2
DOUTP_F_A1: C163.2, D11.C, J14.SIG, L20.2, R100.2
DOUTP_F_A2: C303.2, D17.C, J24.SIG, L39.2, R181.2
DOUTP_F_A3: C443.2, D23.C, J34.SIG, L58.2, R262.2
DOUTP_F_B: C44.2, D1.C, J1.SIG, L1.2, R3.2
DOUTP_F_B1: C226.2, D12.C, J18.SIG, L31.2, R138.2
DOUTP_F_B2: C366.2, D18.C, J28.SIG, L50.2, R219.2
DOUTP_F_B3: C506.2, D24.C, J38.SIG, L69.2, R300.2
FMC_PG: J9.D1, J9.F1
FMC_PG1: J17.D1, J17.F1
FMC_PG2: J27.D1, J27.F1
FMC_PG3: J37.D1, J37.F1
GND: C1.1, C2.1, C3.1, C4.1, C5.1, C6.1, C10.1, C11.1, C12.1, C13.2, C14.2, C15.2, C16.2, C20.1, C21.1, C22.2, C23.2, C24.1, C25.1, C26.1, C27.1, C28.2, C29.2, C30.2, C31.2, C32.2, C33.2, C34.1, C35.1, C36.1, C37.1, C40.1, C41.1, C42.1, C43.1, C46.1, C47.1, C48.1, C49.1, C50.1, C51.1, C52.1, C53.1, C54.1, C55.1, C56.1, C57.1, C58.1, C60.1, C61.1, C63.1, C64.1, C65.1, C66.1, C67.1, C68.1, C70.1, C71.1, C72.1, C73.1, C74.1, C75.1, C76.1, C78.1, C79.1, C80.1, C82.1, C86.1, C87.1, C89.1, C91.1, C92.1, C93.1, C94.1, C96.1, C97.1, C98.1, C102.1, C106.1, C109.1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
GND1: C141.2, C142.2, C143.1, C144.2, C145.2, C146.1, C147.1, C148.1, C149.1, C150.1, C151.1, C152.1, C153.1, C154.1, C155.1, C156.1, C157.1, C158.1, C159.1, C160.1, C161.1, C162.1, C165.2, C166.1, C167.2, C168.1, C169.1, C170.1, C171.1, C172.1, C173.1, C174.1, C175.1, C176.2, C177.2, C178.2, C179.1, C180.2, C181.1, C182.2, C183.1, C184.1, C188.1, C197.1, C198.2, C199.1, C200.1, C201.2, C202.1, C203.1, C204.1, C213.1, C214.1, C215.1, C222.1, C223.1, C224.1, C225.1, C228.2, C229.1, C230.2, C231.1, C232.1, C233.1, C234.1, C235.2, C236.2, C237.2, C238.2, C239.1, C240.1, C241.1, C242.1, C243.1, C244.1, C245.1, C246.1, C247.1, C248.1, C249.1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
GND2: C281.2, C282.2, C283.1, C284.2, C285.2, C286.1, C287.1, C288.1, C289.1, C290.1, C291.1, C292.1, C293.1, C294.1, C295.1, C296.1, C297.1, C298.1, C299.1, C300.1, C301.1, C302.1, C305.2, C306.1, C307.2, C308.1, C309.1, C310.1, C311.1, C312.1, C313.1, C314.1, C315.1, C316.2, C317.2, C318.2, C319.1, C320.2, C321.1, C322.2, C323.1, C324.1, C328.1, C337.1, C338.2, C339.1, C340.1, C341.2, C342.1, C343.1, C344.1, C353.1, C354.1, C355.1, C362.1, C363.1, C364.1, C365.1, C368.2, C369.1, C370.2, C371.1, C372.1, C373.1, C374.1, C375.2, C376.2, C377.2, C378.2, C379.1, C380.1, C381.1, C382.1, C383.1, C384.1, C385.1, C386.1, C387.1, C388.1, C389.1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
GND3: C421.2, C422.2, C423.1, C424.2, C425.2, C426.1, C427.1, C428.1, C429.1, C430.1, C431.1, C432.1, C433.1, C434.1, C435.1, C436.1, C437.1, C438.1, C439.1, C440.1, C441.1, C442.1, C445.2, C446.1, C447.2, C448.1, C449.1, C450.1, C451.1, C452.1, C453.1, C454.1, C455.1, C456.2, C457.2, C458.2, C459.1, C460.2, C461.1, C462.2, C463.1, C464.1, C468.1, C477.1, C478.2, C479.1, C480.1, C481.2, C482.1, C483.1, C484.1, C493.1, C494.1, C495.1, C502.1, C503.1, C504.1, C505.1, C508.2, C509.1, C510.2, C511.1, C512.1, C513.1, C514.1, C515.2, C516.2, C517.2, C518.2, C519.1, C520.1, C521.1, C522.1, C523.1, C524.1, C525.1, C526.1, C527.1, C528.1, C529.1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
LINK_A_PWR_EN: J9.H37, R68.1, U17.B2
LINK_A_PWR_EN1: J17.H37, R137.1, U27.B2
LINK_A_PWR_EN2: J27.H37, R218.1, U50.B2
LINK_A_PWR_EN3: J37.H37, R299.1, U73.B2
LINK_B_PWR_EN: J9.K38, R67.1, U17.D2
LINK_B_PWR_EN1: J17.K38, R118.1, U27.D2
LINK_B_PWR_EN2: J27.K38, R199.1, U50.D2
LINK_B_PWR_EN3: J37.K38, R280.1, U73.D2
LINK_PWR_ADJ_MISO: J9.F37, R69.2, U16.15
LINK_PWR_ADJ_MISO1: J17.F37, R162.2, U36.15
LINK_PWR_ADJ_MISO2: J27.F37, R243.2, U59.15
LINK_PWR_ADJ_MISO3: J37.F37, R324.2, U82.15
LINK_PWR_ADJ_MOSI: J9.E36, U16.14
LINK_PWR_ADJ_MOSI1: J17.E36, U36.14
LINK_PWR_ADJ_MOSI2: J27.E36, U59.14
LINK_PWR_ADJ_MOSI3: J37.E36, U82.14
LINK_PWR_ADJ_SCLK: J9.H38, U16.13
LINK_PWR_ADJ_SCLK1: J17.H38, U36.13
LINK_PWR_ADJ_SCLK2: J27.H38, U59.13
LINK_PWR_ADJ_SCLK3: J37.H38, U82.13
LVDS_DIN0: J9.J2, U3.3
LVDS_DIN0_N: J7.4, R25.1, U3.1
LVDS_DIN0_N1: J16.4, R153.1, U39.1
LVDS_DIN0_N2: J26.4, R234.1, U62.1
LVDS_DIN0_N3: J36.4, R315.1, U85.1
LVDS_DIN0_P: J7.17, R25.2, U3.2
LVDS_DIN0_P1: J16.17, R153.2, U39.2
LVDS_DIN0_P2: J26.17, R234.2, U62.2
LVDS_DIN0_P3: J36.17, R315.2, U85.2
LVDS_DIN1: J9.H5, U3.5
LVDS_DIN1_N: J7.16, R26.1, U3.7
LVDS_DIN1_N1: J16.16, R154.1, U39.7
LVDS_DIN1_N2: J26.16, R235.1, U62.7
LVDS_DIN1_N3: J36.16, R316.1, U85.7
LVDS_DIN1_P: J7.3, R26.2, U3.6
LVDS_DIN1_P1: J16.3, R154.2, U39.6
LVDS_DIN1_P2: J26.3, R235.2, U62.6
LVDS_DIN1_P3: J36.3, R316.2, U85.6
LVDS_DIN2: J9.H4, U3.11
LVDS_DIN2_N: J7.2, R27.1, U3.9
LVDS_DIN2_N1: J16.2, R155.1, U39.9
LVDS_DIN2_N2: J26.2, R236.1, U62.9
LVDS_DIN2_N3: J36.2, R317.1, U85.9
LVDS_DIN2_P: J7.15, R27.2, U3.10
LVDS_DIN2_P1: J16.15, R155.2, U39.10
LVDS_DIN2_P2: J26.15, R236.2, U62.10
LVDS_DIN2_P3: J36.15, R317.2, U85.10
LVDS_DIN3: J17.H5, U39.5
LVDS_DIN4: J17.J2, U39.3
LVDS_DIN5: J17.H4, U39.11
LVDS_DIN6: J27.H5, U62.5
LVDS_DIN7: J27.J2, U62.3
LVDS_DIN8: J27.H4, U62.11
LVDS_DIN9: J37.H5, U85.5
LVDS_DIN10: J37.J2, U85.3
LVDS_DIN11: J37.H4, U85.11
LVDS_DOUT0: J9.J3, U2.2
LVDS_DOUT0_N: J7.19, U2.7
LVDS_DOUT0_N1: J16.19, U40.7
LVDS_DOUT0_N2: J26.19, U63.7
LVDS_DOUT0_N3: J36.19, U86.7
LVDS_DOUT0_P: J7.6, U2.8
LVDS_DOUT0_P1: J16.6, U40.8
LVDS_DOUT0_P2: J26.6, U63.8
LVDS_DOUT0_P3: J36.6, U86.8
LVDS_DOUT1: J9.K4, U2.3
LVDS_DOUT1_N: J7.18, U2.5
LVDS_DOUT1_N1: J16.18, U40.5
LVDS_DOUT1_N2: J26.18, U63.5
LVDS_DOUT1_N3: J36.18, U86.5
LVDS_DOUT1_P: J7.5, U2.6
LVDS_DOUT1_P1: J16.5, U40.6
LVDS_DOUT1_P2: J26.5, U63.6
LVDS_DOUT1_P3: J36.5, U86.6
LVDS_DOUT2: J17.K4, U40.3
LVDS_DOUT3: J17.J3, U40.2
LVDS_DOUT4: J27.K4, U63.3
LVDS_DOUT5: J27.J3, U63.2
LVDS_DOUT6: J37.K4, U86.3
LVDS_DOUT7: J37.J3, U86.2
MLVDS_CLK_0_N: J6.10, U11.24
MLVDS_CLK_0_N1: J19.10, U38.24
MLVDS_CLK_0_N2: J29.10, U61.24
MLVDS_CLK_0_N3: J39.10, U84.24
MLVDS_CLK_0_P: J6.09, U11.23
MLVDS_CLK_0_P1: J19.09, U38.23
MLVDS_CLK_0_P2: J29.09, U61.23
MLVDS_CLK_0_P3: J39.09, U84.23
MLVDS_CLK_1_N: J6.08, U11.22
MLVDS_CLK_1_N1: J19.08, U38.22
MLVDS_CLK_1_N2: J29.08, U61.22
MLVDS_CLK_1_N3: J39.08, U84.22
MLVDS_CLK_1_P: J6.07, U11.21
MLVDS_CLK_1_P1: J19.07, U38.21
MLVDS_CLK_1_P2: J29.07, U61.21
MLVDS_CLK_1_P3: J39.07, U84.21
MLVDS_CLK_2_N: J6.04, U11.20
MLVDS_CLK_2_N1: J19.04, U38.20
MLVDS_CLK_2_N2: J29.04, U61.20
MLVDS_CLK_2_N3: J39.04, U84.20
MLVDS_CLK_2_P: J6.03, U11.19
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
